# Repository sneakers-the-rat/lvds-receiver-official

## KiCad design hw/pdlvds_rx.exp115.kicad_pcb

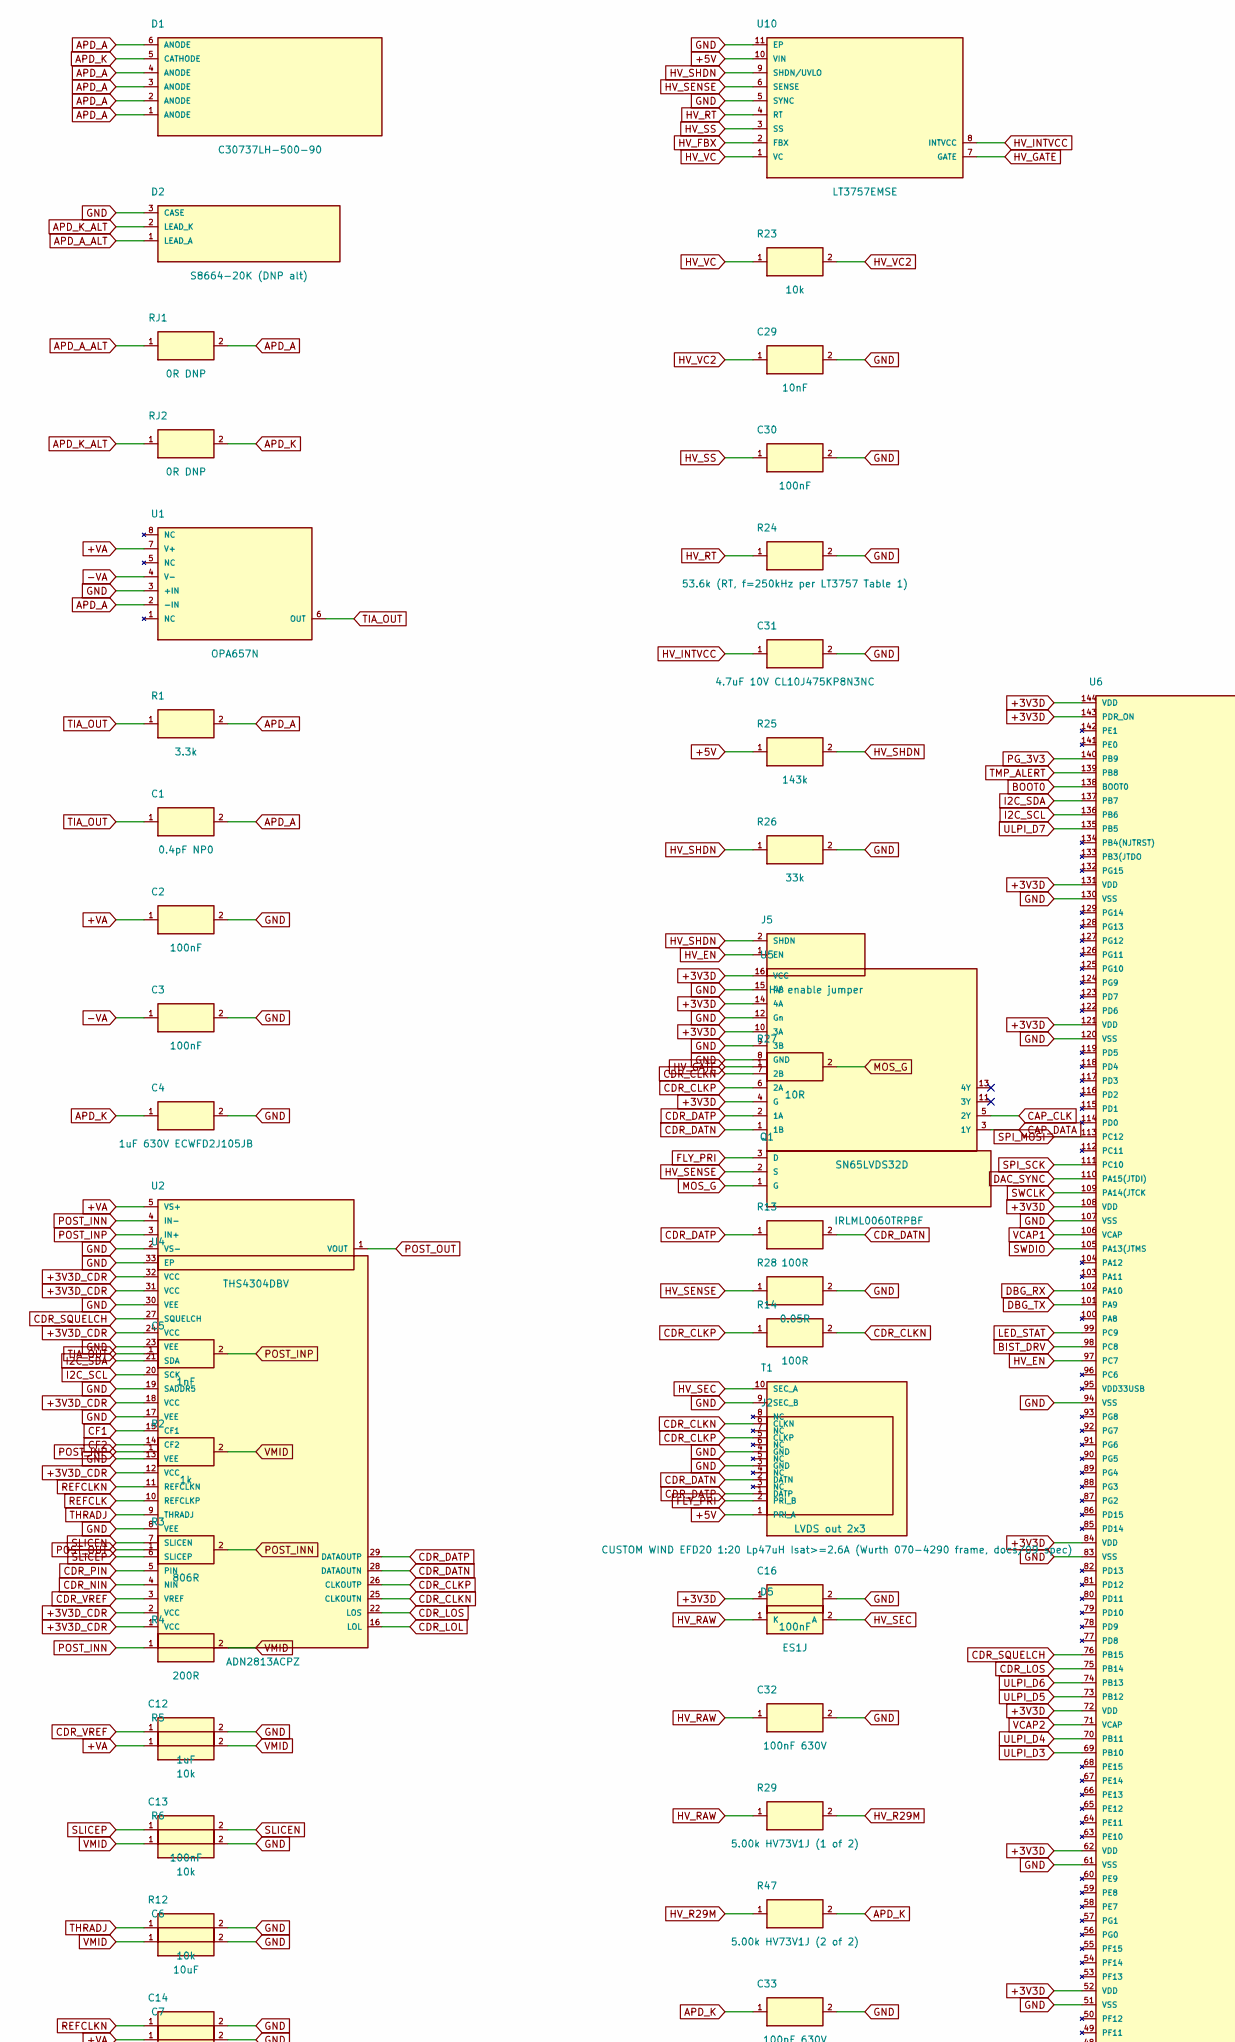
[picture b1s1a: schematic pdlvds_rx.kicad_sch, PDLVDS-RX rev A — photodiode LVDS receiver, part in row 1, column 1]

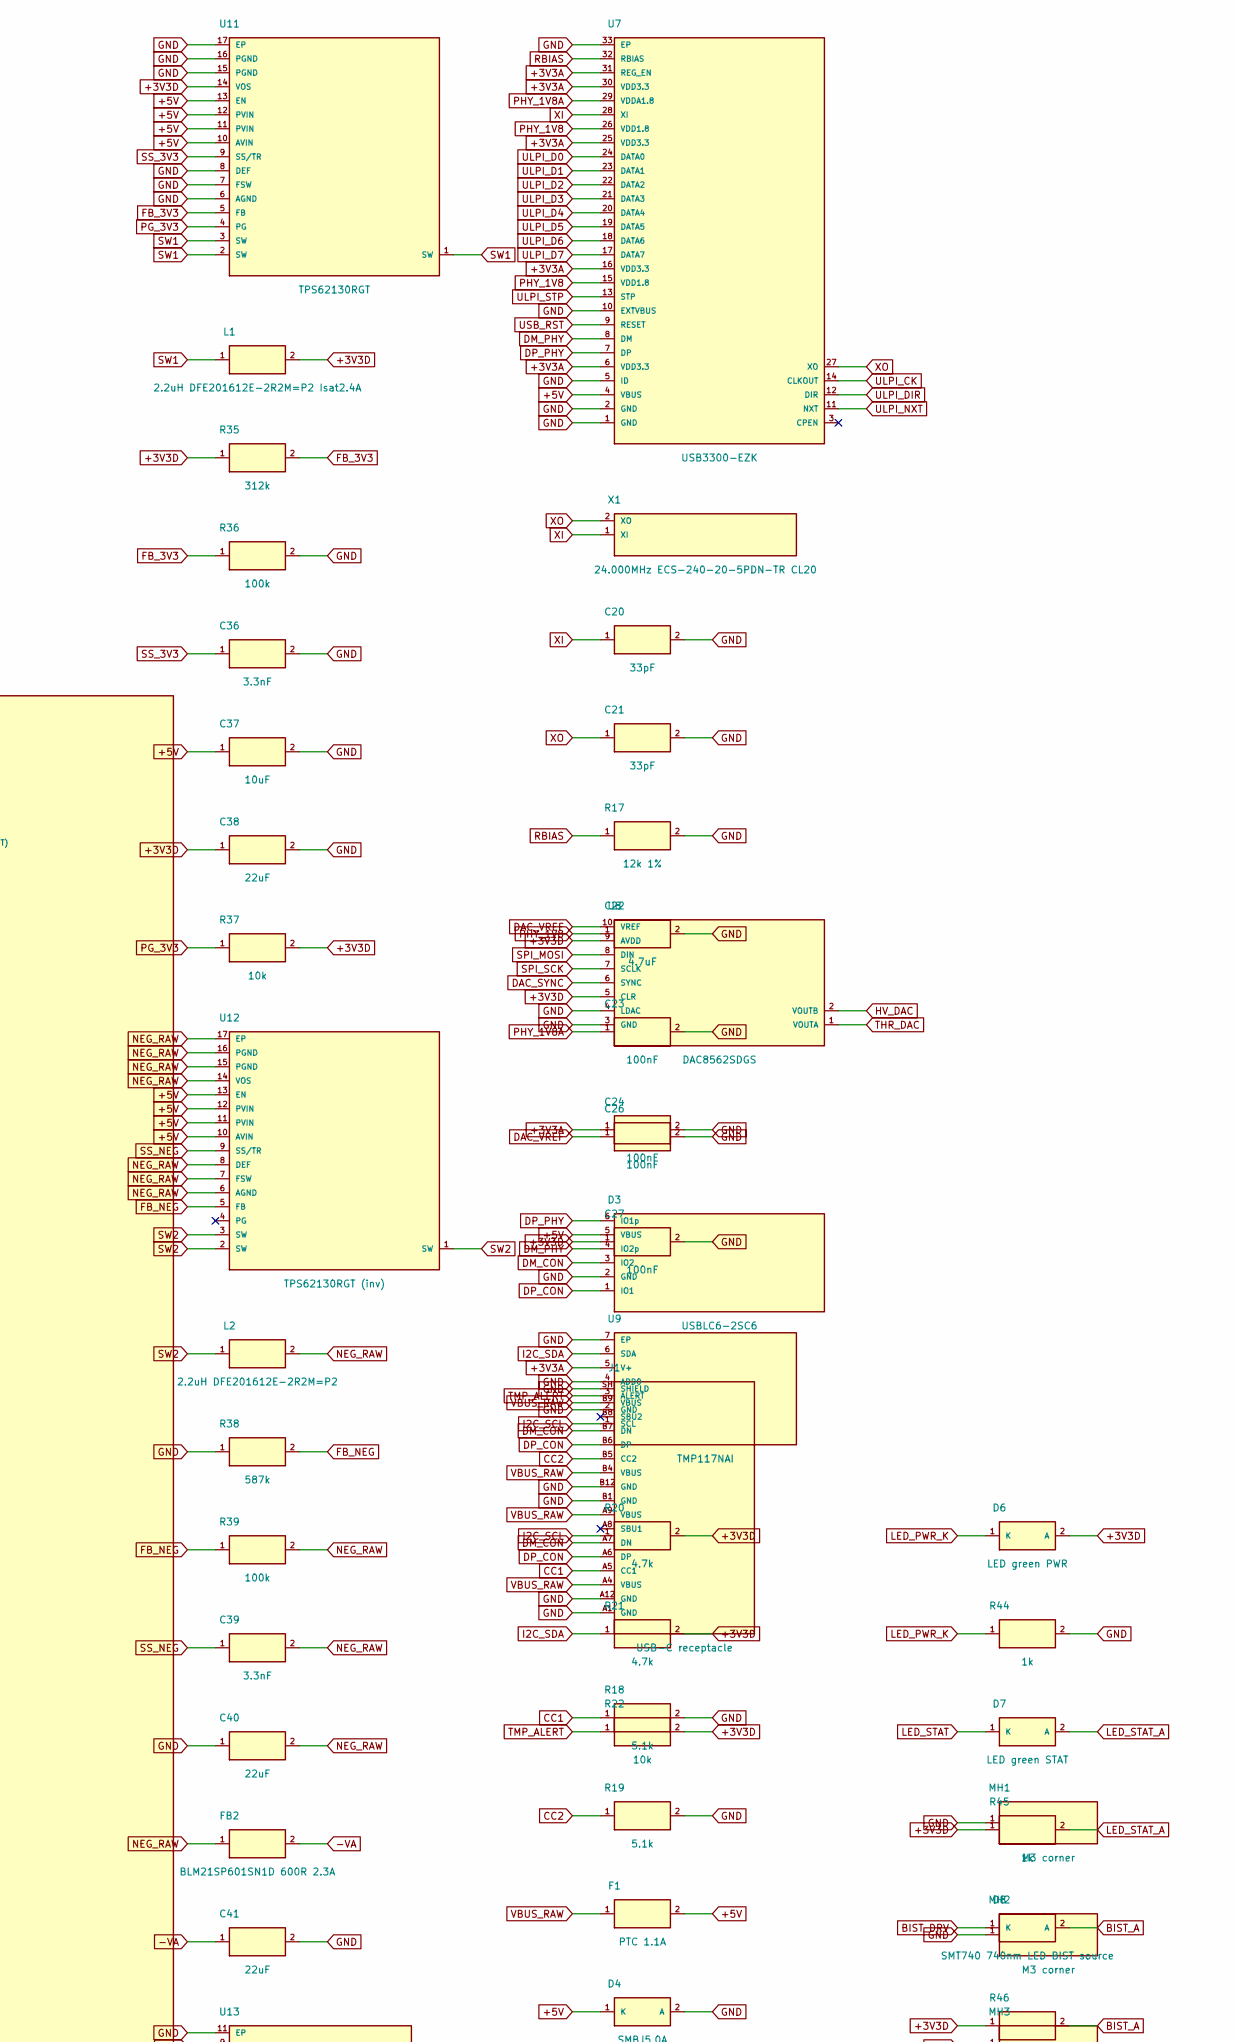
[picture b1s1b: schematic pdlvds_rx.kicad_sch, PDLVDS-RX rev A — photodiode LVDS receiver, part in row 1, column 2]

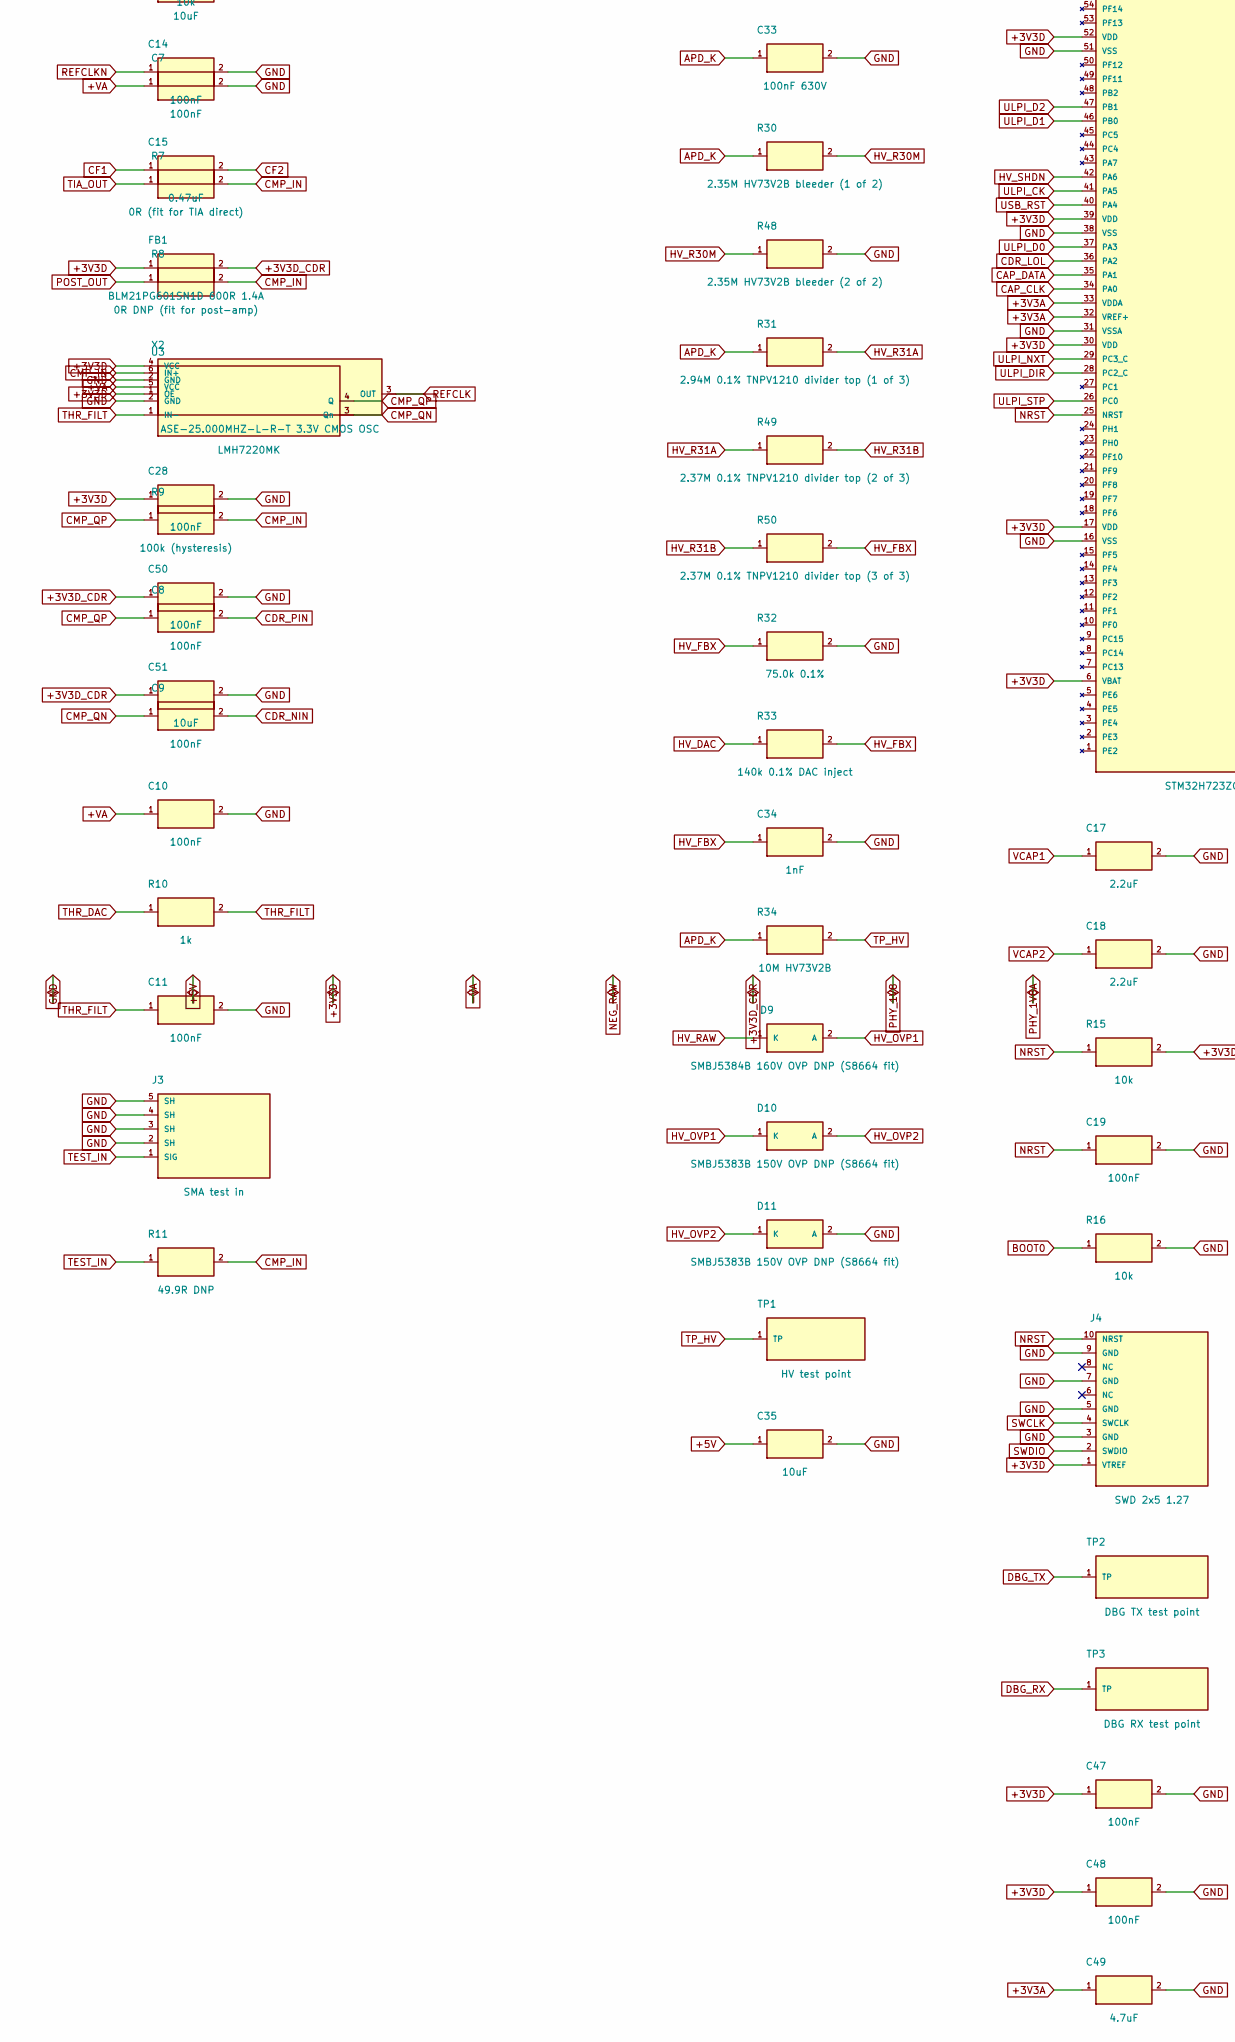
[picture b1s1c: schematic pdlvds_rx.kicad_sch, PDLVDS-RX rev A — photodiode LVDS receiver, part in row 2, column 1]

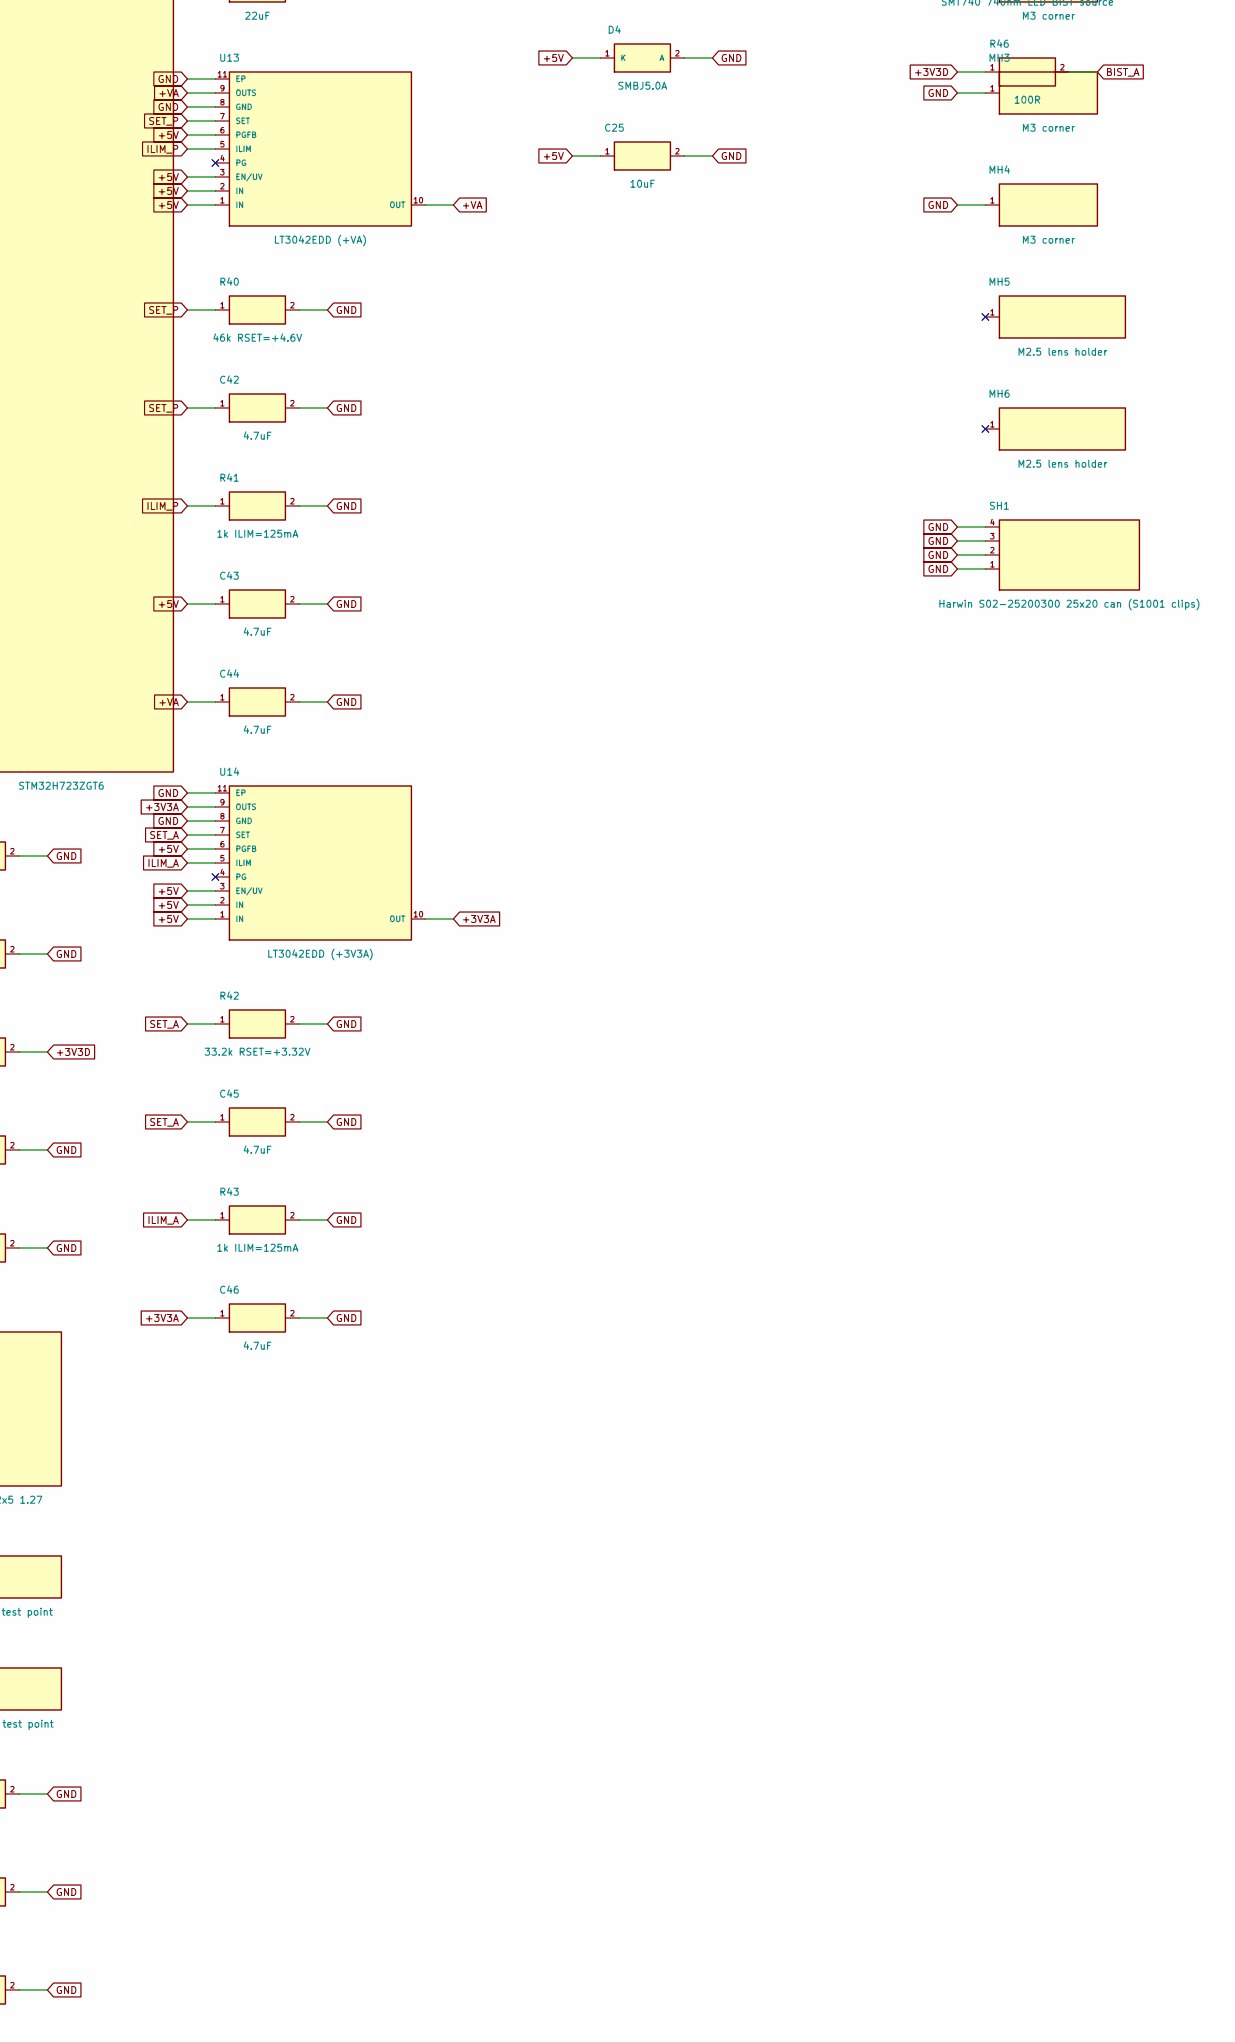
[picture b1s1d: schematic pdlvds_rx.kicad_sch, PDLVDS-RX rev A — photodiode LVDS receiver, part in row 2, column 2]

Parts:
C1: 0.4pF NP0; C_0402_1005Metric
C2, C3, C7, C8, C9, C10, C11, C13, C14, C16, C19, C23, C24, C26, C27, C28, C30, C47, C48, C50: 100nF; C_0603_1608Metric
C4: 1uF 630V ECWFD2J105JB; ECWFD_1uF_630V
C5, C34: 1nF; C_0603_1608Metric
C6, C25, C35, C37, C51: 10uF; C_0805_2012Metric
C12: 1uF; C_0603_1608Metric
C15: 0.47uF; C_0603_1608Metric
C17, C18: 2.2uF; C_0603_1608Metric
C20, C21: 33pF; C_0603_1608Metric
C22, C42, C43, C44, C45, C46, C49: 4.7uF; C_0603_1608Metric
C29: 10nF; C_0603_1608Metric
C31: 4.7uF 10V CL10J475KP8N3NC; C_0603_1608Metric
C32, C33: 100nF 630V; C_1206_3216Metric
C36, C39: 3.3nF; C_0603_1608Metric
C38, C40, C41: 22uF; C_0805_2012Metric
D1: C30737LH-500-90; C30737LH_LCC6
D2: S8664-20K (DNP alt); S8664_TO5
D3: USBLC6-2SC6; SOT-23-6
D4: SMBJ5.0A; D_SMB
D5: ES1J; D_SMA
D6: LED green PWR; LED_0603_1608Metric
D7: LED green STAT; LED_0603_1608Metric
D8: SMT740 740nm LED BIST source; LED_1206_3216Metric
D9: SMBJ5384B 160V OVP DNP (S8664 fit); D_SMB
D10, D11: SMBJ5383B 150V OVP DNP (S8664 fit); D_SMB
F1: PTC 1.1A; Fuse_1812_4532Metric
FB1: BLM21PG601SN1D 600R 1.4A; L_0805_2012Metric
FB2: BLM21SP601SN1D 600R 2.3A; L_0805_2012Metric
J1: USB-C receptacle; USB_C_Receptacle_Amphenol_12401610E4-2A
J2: LVDS out 2x3; PinHeader_2x03_P2.54mm_Vertical
J3: SMA test in; SMA_Amphenol_132134_Vertical
J4: SWD 2x5 1.27; PinHeader_2x05_P1.27mm_Vertical
J5: HV enable jumper; PinHeader_1x02_P2.54mm_Vertical
L1: 2.2uH DFE201612E-2R2M=P2 Isat2.4A; L_Murata_DFE201610P
L2: 2.2uH DFE201612E-2R2M=P2; L_Murata_DFE201610P
MH1, MH2, MH3, MH4: M3 corner; MountingHole_3.2mm_M3
MH5, MH6: M2.5 lens holder; MountingHole_2.7mm_M2.5
Q1: IRLML0060TRPBF; SOT-23
R1: 3.3k; R_0603_1608Metric
R2, R10, R44, R45: 1k; R_0603_1608Metric
R3: 806R; R_0603_1608Metric
R4: 200R; R_0603_1608Metric
R5, R6, R12, R15, R16, R22, R23, R37: 10k; R_0603_1608Metric
R7: 0R (fit for TIA direct); R_0603_1608Metric
R8: 0R DNP (fit for post-amp); R_0603_1608Metric
R9: 100k (hysteresis); R_0603_1608Metric
R11: 49.9R DNP; R_0603_1608Metric
R13, R14, R46: 100R; R_0603_1608Metric
R17: 12k 1%; R_0603_1608Metric
R18, R19: 5.1k; R_0603_1608Metric
R20, R21: 4.7k; R_0603_1608Metric
R24: 53.6k (RT, f=250kHz per LT3757 Table 1); R_0603_1608Metric
R25: 143k; R_0603_1608Metric
R26: 33k; R_0603_1608Metric
R27: 10R; R_0603_1608Metric
R28: 0.05R; R_1206_3216Metric
R29: 5.00k HV73V1J (1 of 2); R_0603_1608Metric
R30: 2.35M HV73V2B bleeder (1 of 2); R_1206_3216Metric
R31: 2.94M 0.1% TNPV1210 divider top (1 of 3); R_1210_3225Metric
R32: 75.0k 0.1%; R_0603_1608Metric
R33: 140k 0.1% DAC inject; R_0603_1608Metric
R34: 10M HV73V2B; R_1206_3216Metric
R35: 312k; R_0603_1608Metric
R36, R39: 100k; R_0603_1608Metric
R38: 587k; R_0603_1608Metric
R40: 46k RSET=+4.6V; R_0603_1608Metric
R41, R43: 1k ILIM=125mA; R_0603_1608Metric
R42: 33.2k RSET=+3.32V; R_0603_1608Metric
R47: 5.00k HV73V1J (2 of 2); R_0603_1608Metric
R48: 2.35M HV73V2B bleeder (2 of 2); R_1206_3216Metric
R49: 2.37M 0.1% TNPV1210 divider top (2 of 3); R_1210_3225Metric
R50: 2.37M 0.1% TNPV1210 divider top (3 of 3); R_1210_3225Metric
RJ1, RJ2: 0R DNP; R_0603_1608Metric
SH1: Harwin S02-25200300 25x20 can (S1001 clips); SHIELD_CAN_26x20
T1: CUSTOM WIND EFD20 1:20 Lp47uH Isat>=2.6A (Wurth 0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; XFMR_EFD20_SMD10
TP1: HV test point; TestPoint_Pad_D1.5mm
TP2: DBG TX test point; TestPoint_Pad_D1.5mm
TP3: DBG RX test point; TestPoint_Pad_D1.5mm
U1: OPA657N; SOIC-8_3.9x4.9mm_P1.27mm
U2: THS4304DBV; SOT-23-5
U3: LMH7220MK; TSOT-23-6
U4: ADN2813ACPZ; QFN-32-1EP_5x5mm_P0.5mm_EP3.1x3.1mm
U5: SN65LVDS32D; SOIC-16_3.9x9.9mm_P1.27mm
U6: STM32H723ZGT6; LQFP-144_20x20mm_P0.5mm
U7: USB3300-EZK; QFN-32-1EP_5x5mm_P0.5mm_EP3.1x3.1mm
U8: DAC8562SDGS; VSSOP-10_3x3mm_P0.5mm
U9: TMP117NAI; TMP117_WSON6
U10: LT3757EMSE; MSOP-10-1EP_3x3mm_P0.5mm_EP1.68x1.88mm
U11: TPS62130RGT; QFN-16-1EP_3x3mm_P0.5mm_EP1.45x1.45mm
U12: TPS62130RGT (inv); QFN-16-1EP_3x3mm_P0.5mm_EP1.45x1.45mm
U13: LT3042EDD (+VA); DFN-10-1EP_3x3mm_P0.5mm_EP1.55x2.48mm
U14: LT3042EDD (+3V3A); DFN-10-1EP_3x3mm_P0.5mm_EP1.55x2.48mm
X1: 24.000MHz ECS-240-20-5PDN-TR CL20; Crystal_SMD_HC49-SD
X2: ASE-25.000MHZ-L-R-T 3.3V CMOS OSC; Oscillator_SMD_Abracon_ASE-4Pin_3.2x2.5mm

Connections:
+3V3A: C24.1, C46.1, C49.1, U6.32 (VREF+), U6.33 (VDDA), U7.6 (VDD3.3), U7.16 (VDD3.3), U7.25 (VDD3.3), U7.30 (VDD3.3), U7.31 (REG_EN), U9.5 (V+), U14.9 (OUTS), U14.10 (OUT); also elsewhere on the board
+3V3D: C16.1, C27.1, C28.1, C38.1, C47.1, C48.1, D6.2 (A), FB1.1, J4.1 (VTREF), L1.2, R15.2, R20.2, R21.2, R22.2, R35.1, R37.2, R45.1, R46.1, U5.4 (G), U5.10 (3A), U5.14 (4A), U5.16 (VCC), U6.6 (VBAT), U6.17 (VDD), U6.30 (VDD), U6.39 (VDD), U6.52 (VDD), U6.62 (VDD), U6.72 (VDD), U6.84 (VDD), U6.108 (VDD), U6.121 (VDD), U6.131 (VDD), U6.143 (PDR_ON), U6.144 (VDD), U8.5 (CLR), U8.9 (AVDD), U11.14 (VOS), X2.1 (OE), X2.4 (VCC)
+3V3D_CDR: C50.1, C51.1, FB1.2, U4.1 (VCC), U4.2 (VCC), U4.12 (VCC), U4.18 (VCC), U4.24 (VCC), U4.31 (VCC), U4.32 (VCC)
+5V: C25.1, C35.1, C37.1, C43.1, D3.5 (VBUS), D4.1 (K), F1.2, R25.1, T1.1 (PRI_A), U7.4 (VBUS), U10.10 (VIN), U11.10 (AVIN), U11.11 (PVIN), U11.12 (PVIN), U11.13 (EN), U12.10 (AVIN), U12.11 (PVIN), U12.12 (PVIN), U12.13 (EN), U13.1 (IN), U13.2 (IN), U13.3 (EN/UV), U13.6 (PGFB), U14.1 (IN), U14.2 (IN), U14.3 (EN/UV), U14.6 (PGFB); also elsewhere on the board
+VA: C2.1, C7.1, C10.1, C44.1, R5.1, U1.7 (V+), U2.5 (VS+), U3.5 (VCC), U13.9 (OUTS), U13.10 (OUT)
-VA: C3.1, C41.1, FB2.2, U1.4 (V-)
APD_A: C1.2, D1.1 (ANODE), D1.2 (ANODE), D1.3 (ANODE), D1.4 (ANODE), D1.6 (ANODE), R1.2, RJ1.2, U1.2 (-IN); also elsewhere on the board
APD_A_ALT: D2.1 (LEAD_A), RJ1.1; also elsewhere on the board
APD_K: C4.1, C33.1, D1.5 (CATHODE), R30.1, R31.1, R34.1, R47.2, RJ2.2; also elsewhere on the board
APD_K_ALT: D2.2 (LEAD_K), RJ2.1; also elsewhere on the board
BIST_A: D8.2 (A), R46.2
BIST_DRV: D8.1 (K), U6.98 (PC8)
BOOT0: R16.1, U6.138 (BOOT0)
CAP_CLK: U5.5 (2Y), U6.34 (PA0)
CAP_DATA: U5.3 (1Y), U6.35 (PA1)
CC1: J1.A5 (CC1), R18.1
CC2: J1.B5 (CC2), R19.1
CDR_CLKN: J2.6 (CLKN), R14.2, U4.25 (CLKOUTN), U5.7 (2B)
CDR_CLKP: J2.5 (CLKP), R14.1, U4.26 (CLKOUTP), U5.6 (2A)
CDR_DATN: J2.2 (DATN), R13.2, U4.28 (DATAOUTN), U5.1 (1B)
CDR_DATP: J2.1 (DATP), R13.1, U4.29 (DATAOUTP), U5.2 (1A)
CDR_LOL: U4.16 (LOL), U6.36 (PA2)
CDR_LOS: U4.22 (LOS), U6.75 (PB14)
CDR_NIN: C9.2, U4.4 (NIN)
CDR_PIN: C8.2, U4.5 (PIN)
CDR_SQUELCH: U4.27 (SQUELCH), U6.76 (PB15)
CDR_VREF: C12.1, U4.3 (VREF)
CF1: C15.1, U4.15 (CF1)
CF2: C15.2, U4.14 (CF2)
CMP_IN: R7.2, R8.2, R9.2, R11.2, U3.6 (IN+)
CMP_QN: C9.1, U3.3 (Qn)
CMP_QP: C8.1, R9.1, U3.4 (Q)
DAC_SYNC: U6.110 (PA15(JTDI)), U8.6 (SYNC)
DAC_VREF: C26.1, U8.10 (VREF)
DBG_RX: TP3.1, U6.102 (PA10)
DBG_TX: TP2.1, U6.101 (PA9)
DM_CON: D3.3 (IO2), J1.A7 (DN), J1.B7 (DN)
DM_PHY: D3.4 (IO2p), U7.8 (DM)
DP_CON: D3.1 (IO1), J1.A6 (DP), J1.B6 (DP)
DP_PHY: D3.6 (IO1p), U7.7 (DP)
FB_3V3: R35.2, R36.1, U11.5 (FB)
FB_NEG: R38.2, R39.1, U12.5 (FB)
FLY_PRI: Q1.3 (D), T1.2 (PRI_B); also elsewhere on the board
GND: C2.2, C3.2, C4.2, C6.2, C7.2, C10.2, C11.2, C12.2, C14.2, C16.2, C17.2, C18.2, C19.2, C20.2, C21.2, C22.2, C23.2, C24.2, C25.2, C26.2, C27.2, C28.2, C29.2, C30.2, C31.2, C32.2, C33.2, C34.2, C35.2, C36.2, C37.2, C38.2, C40.1, C41.2, C42.2, C43.2, C44.2, C45.2, C46.2, C47.2, C48.2, C49.2, C50.2, C51.2, D2.3 (CASE), D3.2 (GND), D4.2 (A), D11.2 (A), J1.A1 (GND), J1.A12 (GND), J1.B1 (GND), J1.B12 (GND), J1.SH (SHIELD), J2.3 (GND), J2.4 (GND), J3.2 (SH), J3.3 (SH), J3.4 (SH), J3.5 (SH), J4.3 (GND), J4.5 (GND), J4.7 (GND), J4.9 (GND), MH1.1, MH2.1, MH3.1, MH4.1, R6.2, R12.2, R16.2, R17.2, R18.2, R19.2, R24.2, R26.2, R28.2, R32.2, R36.2, R38.1, R40.2, R41.2, R42.2, R43.2, R44.2, R48.2, SH1.1, SH1.2, SH1.3, SH1.4, T1.9 (SEC_B), U1.3 (+IN), U2.2 (VS-), U3.2 (GND), U4.8 (VEE), U4.13 (VEE), U4.17 (VEE), U4.19 (SADDR5), U4.23 (VEE), U4.30 (VEE), U4.33 (EP), U5.8 (GND), U5.9 (3B), U5.12 (Gn), U5.15 (4B), U6.16 (VSS), U6.31 (VSSA), U6.38 (VSS), U6.51 (VSS), U6.61 (VSS), U6.83 (VSS), U6.94 (VSS), U6.107 (VSS), U6.120 (VSS), U6.130 (VSS), U7.1 (GND), U7.2 (GND), U7.5 (ID), U7.10 (EXTVBUS), U7.33 (EP), U8.3 (GND), U8.4 (LDAC), U9.2 (GND), U9.4 (ADD0), U9.7 (EP), U10.5 (SYNC), U10.11 (EP), U11.6 (AGND), U11.7 (FSW), U11.8 (DEF), U11.15 (PGND), U11.16 (PGND), U11.17 (EP), U13.8 (GND), U13.11 (EP), U14.8 (GND), U14.11 (EP), X2.2 (GND); also elsewhere on the board
HV_DAC: R33.1, U8.2 (VOUTB)
HV_EN: J5.1 (EN), U6.97 (PC7)
HV_FBX: C34.1, R32.1, R33.2, R50.2, U10.2 (FBX)
HV_GATE: R27.1, U10.7 (GATE)
HV_INTVCC: C31.1, U10.8 (INTVCC)
HV_OVP1: D9.2 (A), D10.1 (K)
HV_OVP2: D10.2 (A), D11.1 (K)
HV_R29M: R29.2, R47.1
HV_R30M: R30.2, R48.1
HV_R31A: R31.2, R49.1
HV_R31B: R49.2, R50.1
HV_RAW: C32.1, D5.1 (K), D9.1 (K), R29.1
HV_RT: R24.1, U10.4 (RT)
HV_SEC: D5.2 (A), T1.10 (SEC_A); also elsewhere on the board
HV_SENSE: Q1.2 (S), R28.1, U10.6 (SENSE)
HV_SHDN: J5.2 (SHDN), R25.2, R26.1, U6.42 (PA6), U10.9 (SHDN/UVLO)
HV_SS: C30.1, U10.3 (SS)
HV_VC: R23.1, U10.1 (VC)
HV_VC2: C29.1, R23.2
I2C_SCL: R20.1, U4.20 (SCK), U6.136 (PB6), U9.1 (SCL); also elsewhere on the board
I2C_SDA: R21.1, U4.21 (SDA), U6.137 (PB7), U9.6 (SDA); also elsewhere on the board
ILIM_A: R43.1, U14.5 (ILIM)
ILIM_P: R41.1, U13.5 (ILIM)
LED_PWR_K: D6.1 (K), R44.1
LED_STAT: D7.1 (K), U6.99 (PC9)
LED_STAT_A: D7.2 (A), R45.2
MOS_G: Q1.1 (G), R27.2
NEG_RAW: C39.2, C40.2, FB2.1, L2.2, R39.2, U12.6 (AGND), U12.7 (FSW), U12.8 (DEF), U12.14 (VOS), U12.15 (PGND), U12.16 (PGND), U12.17 (EP)
NRST: C19.1, J4.10 (NRST), R15.1, U6.25 (NRST)
PG_3V3: R37.1, U6.140 (PB9), U11.4 (PG)
PHY_1V8: C22.1, U7.15 (VDD1.8), U7.26 (VDD1.8)
PHY_1V8A: C23.1, U7.29 (VDDA1.8)
POST_INN: R3.2, R4.1, U2.4 (IN-)
POST_INP: C5.2, R2.1, U2.3 (IN+)
POST_OUT: R3.1, R8.1, U2.1 (VOUT)
RBIAS: R17.1, U7.32 (RBIAS)
REFCLK: U4.10 (REFCLKP), X2.3 (OUT)
REFCLKN: C14.1, U4.11 (REFCLKN)
SET_A: C45.1, R42.1, U14.7 (SET)
SET_P: C42.1, R40.1, U13.7 (SET)
SLICEN: C13.2, U4.7 (SLICEN)
SLICEP: C13.1, U4.6 (SLICEP)
SPI_MOSI: U6.113 (PC12), U8.8 (DIN)
SPI_SCK: U6.111 (PC10), U8.7 (SCLK)
SS_3V3: C36.1, U11.9 (SS/TR)
SS_NEG: C39.1, U12.9 (SS/TR)
SW1: L1.1, U11.1 (SW), U11.2 (SW), U11.3 (SW)
SW2: L2.1, U12.1 (SW), U12.2 (SW), U12.3 (SW)
SWCLK: J4.4 (SWCLK), U6.109 (PA14(JTCK)
SWDIO: J4.2 (SWDIO), U6.105 (PA13(JTMS)
TEST_IN: J3.1 (SIG), R11.1
THRADJ: R12.1, U4.9 (THRADJ)
THR_DAC: R10.1, U8.1 (VOUTA)
THR_FILT: C11.1, R10.2, U3.1 (IN-)
TIA_OUT: C1.1, C5.1, R1.1, R7.1, U1.6 (OUT)
TMP_ALERT: R22.1, U6.139 (PB8), U9.3 (ALERT); also elsewhere on the board
TP_HV: R34.2, TP1.1
ULPI_CK: U6.41 (PA5), U7.14 (CLKOUT)
ULPI_D0: U6.37 (PA3), U7.24 (DATA0)
ULPI_D1: U6.46 (PB0), U7.23 (DATA1)
ULPI_D2: U6.47 (PB1), U7.22 (DATA2)
ULPI_D3: U6.69 (PB10), U7.21 (DATA3)
ULPI_D4: U6.70 (PB11), U7.20 (DATA4)
ULPI_D5: U6.73 (PB12), U7.19 (DATA5)
ULPI_D6: U6.74 (PB13), U7.18 (DATA6)
ULPI_D7: U6.135 (PB5), U7.17 (DATA7)
ULPI_DIR: U6.28 (PC2_C), U7.12 (DIR)
ULPI_NXT: U6.29 (PC3_C), U7.11 (NXT)
ULPI_STP: U6.26 (PC0), U7.13 (STP)
USB_RST: U6.40 (PA4), U7.9 (RESET)
VBUS_RAW: F1.1, J1.A4 (VBUS), J1.A9 (VBUS), J1.B4 (VBUS), J1.B9 (VBUS)
VCAP1: C17.1, U6.106 (VCAP)
VCAP2: C18.1, U6.71 (VCAP)
VMID: C6.1, R2.2, R4.2, R5.2, R6.1
XI: C20.1, U7.28 (XI), X1.1 (XI)
XO: C21.1, U7.27 (XO), X1.2 (XO)

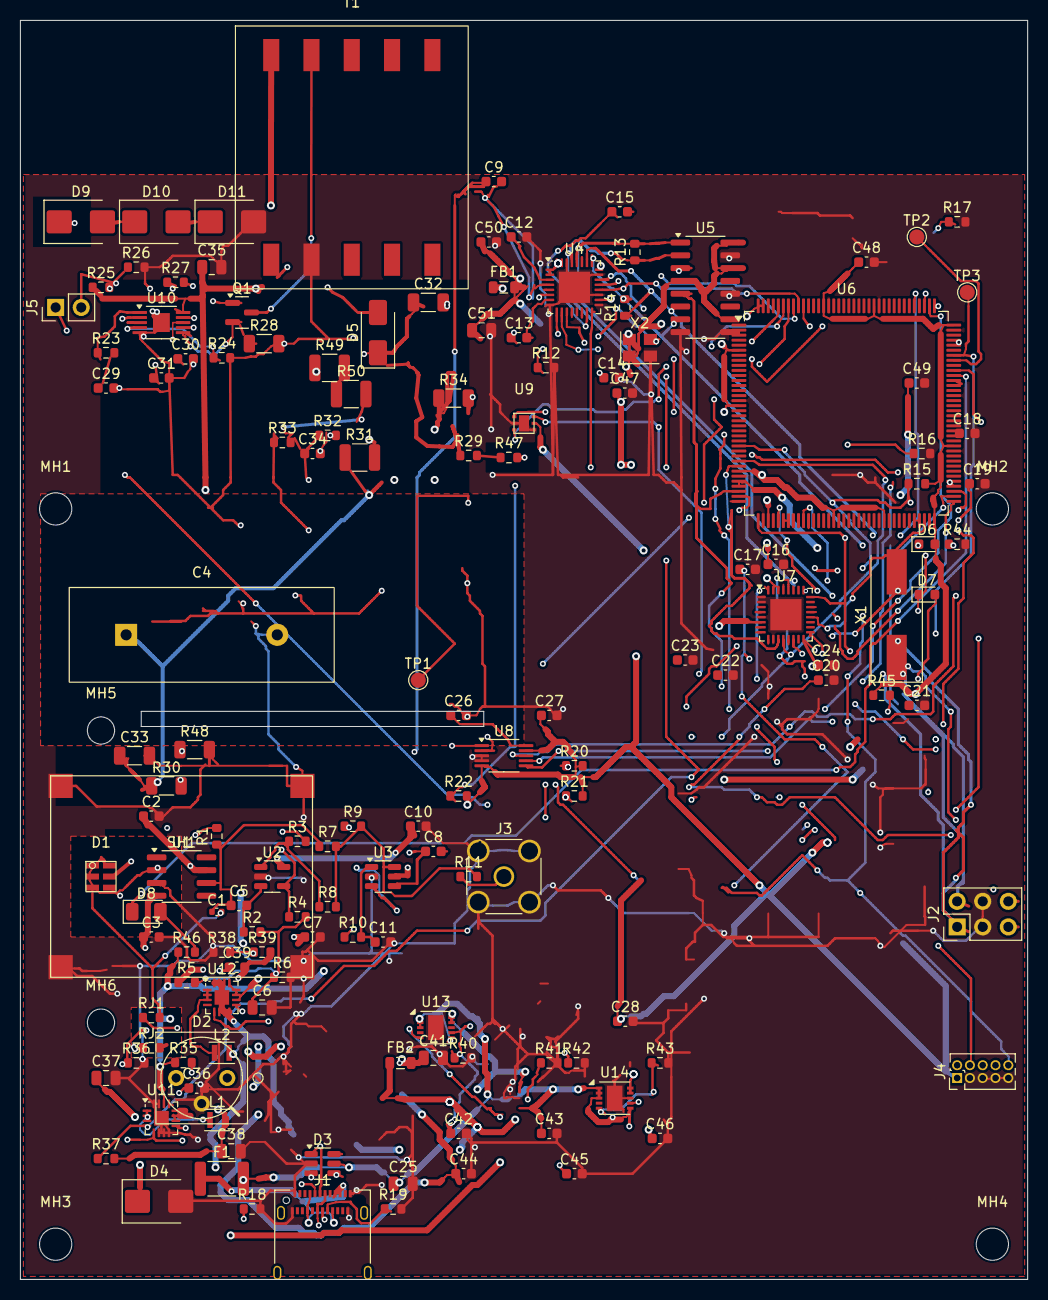
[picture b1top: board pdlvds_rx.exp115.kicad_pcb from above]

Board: 4 copper layers, 100.0 x 125.0 mm, 152 parts (1 on the bottom side), 120 nets.

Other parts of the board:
C: ECWFD2J105JB; ECWFD_1uF_630V
D: S8664; S8664_TO5
D#2: C30737LH; C30737LH_LCC6
SH: SHIELD; SHIELD_CAN_26x20
T: EFD20 custom wind; XFMR_EFD20_SMD10
U: TMP117; TMP117_WSON6

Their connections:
+3V3A: U.5; also elsewhere on the board
+5V: T.1; also elsewhere on the board
APD_A: D#2.1, D#2.2, D#2.3, D#2.4, D#2.6; also elsewhere on the board
APD_A_ALT: D.1; also elsewhere on the board
APD_K: C.1, D#2.5; also elsewhere on the board
APD_K_ALT: D.2; also elsewhere on the board
FLY_PRI: T.2; also elsewhere on the board
GND: C.2, D.3, SH.1, SH.2, SH.3, SH.4, T.9, U.2, U.4, U.7; also elsewhere on the board
HV_SEC: T.10; also elsewhere on the board
I2C_SCL: U.1; also elsewhere on the board
I2C_SDA: U.6; also elsewhere on the board
TMP_ALERT: U.3; also elsewhere on the board

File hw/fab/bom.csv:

Refs,Qty,Value,Footprint
C1,1,0.4pF NP0,Capacitor_SMD:C_0402_1005Metric
C15,1,0.47uF,Capacitor_SMD:C_0603_1608Metric
C17 C18,2,2.2uF,Capacitor_SMD:C_0603_1608Metric
C2 C3 C7 C8 C9 C10 C11 C13 C14 C16 C19 C23 C24 C26 C27 C28 C30 C47 C48 C50,20,100nF,Capacitor_SMD:C_0603_1608Metric
C20 C21,2,18pF,Capacitor_SMD:C_0603_1608Metric
C22 C31 C42 C43 C44 C45 C46 C49,8,4.7uF,Capacitor_SMD:C_0603_1608Metric
C29,1,10nF,Capacitor_SMD:C_0603_1608Metric
C32 C33,2,100nF 630V,Capacitor_SMD:C_1206_3216Metric
C36 C39,2,3.3nF,Capacitor_SMD:C_0603_1608Metric
C38 C40 C41,3,22uF,Capacitor_SMD:C_0805_2012Metric
C4 C12,2,1uF,Capacitor_SMD:C_0603_1608Metric
C5 C34,2,1nF,Capacitor_SMD:C_0603_1608Metric
C6 C25 C35 C37 C51,5,10uF,Capacitor_SMD:C_0805_2012Metric
D1,1,C30737LH-500-90,pdlvds:C30737LH_LCC6
D2,1,S8664-20K (DNP alt),pdlvds:S8664_TO5
D3,1,USBLC6-2SC6,Package_TO_SOT_SMD:SOT-23-6
D4,1,SMBJ5.0A,Diode_SMD:D_SMA
D5,1,ES1J,Diode_SMD:D_SMA
D6,1,LED green PWR,LED_SMD:LED_0603_1608Metric
D7,1,LED green STAT,LED_SMD:LED_0603_1608Metric
D8,1,LED 740nm BIST source,LED_SMD:LED_1206_3216Metric
F1,1,PTC 1.1A,Fuse:Fuse_1812_4532Metric
FB1 FB2,2,600R@100MHz,Inductor_SMD:L_0805_2012Metric
J1,1,USB-C receptacle,Connector_USB:USB_C_Receptacle_Amphenol_12401610E4-2A
J2,1,LVDS out 2x3,Connector_PinHeader_2.54mm:PinHeader_2x03_P2.54mm_Vertical
J3,1,SMA test in,Connector_Coaxial:SMA_Amphenol_132134_Vertical
J4,1,SWD 2x5 1.27,Connector_PinHeader_1.27mm:PinHeader_2x05_P1.27mm_Vertical
J5,1,HV enable jumper,Connector_PinHeader_2.54mm:PinHeader_1x02_P2.54mm_Vertical
L1 L2,2,2.2uH,Inductor_SMD:L_0805_2012Metric
MH1 MH2 MH3 MH4,4,M3 corner,MountingHole:MountingHole_3.2mm_M3
MH5 MH6,2,M2.5 lens holder,MountingHole:MountingHole_2.7mm_M2.5
Q1,1,IRLML0030 SOT-23,Package_TO_SOT_SMD:SOT-23
R1,1,3.3k,Resistor_SMD:R_0603_1608Metric
R11,1,49.9R DNP,Resistor_SMD:R_0603_1608Metric
R13 R14 R46,3,100R,Resistor_SMD:R_0603_1608Metric
R17,1,12k 1%,Resistor_SMD:R_0603_1608Metric
R18 R19,2,5.1k,Resistor_SMD:R_0603_1608Metric
R2 R10 R44 R45,4,1k,Resistor_SMD:R_0603_1608Metric
R20 R21,2,4.7k,Resistor_SMD:R_0603_1608Metric
R24,1,"24.9k (RT, VERIFY f=250k)",Resistor_SMD:R_0603_1608Metric
R25,1,143k,Resistor_SMD:R_0603_1608Metric
R26,1,33k,Resistor_SMD:R_0603_1608Metric
R28,1,0.05R,Resistor_SMD:R_1206_3216Metric
R29,1,10k HV,Resistor_SMD:R_1206_3216Metric
R3,1,806R,Resistor_SMD:R_0603_1608Metric
R30,1,4.7M bleeder,Resistor_SMD:R_1206_3216Metric
R31,1,7.68M 0.1% HV divider top,Resistor_SMD:R_1206_3216Metric
R32,1,75.0k 0.1%,Resistor_SMD:R_0603_1608Metric
R33,1,140k 0.1% DAC inject,Resistor_SMD:R_0603_1608Metric
R34,1,10M HV probe,Resistor_SMD:R_1206_3216Metric
R35,1,312k,Resistor_SMD:R_0603_1608Metric
R36 R39,2,100k,Resistor_SMD:R_0603_1608Metric
R38,1,587k,Resistor_SMD:R_0603_1608Metric
R4,1,200R,Resistor_SMD:R_0603_1608Metric
R40,1,46k RSET=+4.6V,Resistor_SMD:R_0603_1608Metric
R41 R43,2,1k ILIM=125mA,Resistor_SMD:R_0603_1608Metric
R42,1,33.2k RSET=+3.32V,Resistor_SMD:R_0603_1608Metric
R5 R6 R12 R15 R16 R22 R23 R27 R37,9,10k,Resistor_SMD:R_0603_1608Metric
R7,1,0R (fit for TIA direct),Resistor_SMD:R_0603_1608Metric
R8,1,0R DNP (fit for post-amp),Resistor_SMD:R_0603_1608Metric
R9,1,100k (hysteresis),Resistor_SMD:R_0603_1608Metric
RJ1 RJ2,2,0R DNP,Resistor_SMD:R_0603_1608Metric
SH1,1,Shield can frontend,pdlvds:SHIELD_CAN_26x20
T1,1,Flyback xfmr 1:20,pdlvds:XFMR_FLYBACK_6P
TP1,1,HV test point,TestPoint:TestPoint_Pad_D1.5mm
TP2,1,DBG TX test point,TestPoint:TestPoint_Pad_D1.5mm
TP3,1,DBG RX test point,TestPoint:TestPoint_Pad_D1.5mm
U1,1,OPA657N,Package_SO:SOIC-8_3.9x4.9mm_P1.27mm
U10,1,LT3757EMSE,Package_SO:MSOP-10-1EP_3x3mm_P0.5mm_EP1.68x1.88mm
U11,1,TPS62130RGT,Package_DFN_QFN:QFN-16-1EP_3x3mm_P0.5mm_EP1.45x1.45mm
U12,1,TPS62130RGT (inv),Package_DFN_QFN:QFN-16-1EP_3x3mm_P0.5mm_EP1.45x1.45mm
U13,1,LT3042EDD (+VA),Package_DFN_QFN:DFN-10-1EP_3x3mm_P0.5mm_EP1.55x2.48mm
U14,1,LT3042EDD (+3V3A),Package_DFN_QFN:DFN-10-1EP_3x3mm_P0.5mm_EP1.55x2.48mm
U2,1,THS4304DBV,Package_TO_SOT_SMD:SOT-23-5
U3,1,LMH7220MK,Package_TO_SOT_SMD:TSOT-23-6
U4,1,ADN2813ACPZ,Package_DFN_QFN:QFN-32-1EP_5x5mm_P0.5mm_EP3.1x3.1mm
U5,1,SN65LVDS32D,Package_SO:SOIC-16_3.9x9.9mm_P1.27mm
U6,1,STM32H723ZGT6,Package_QFP:LQFP-144_20x20mm_P0.5mm
U7,1,USB3300-EZK,Package_DFN_QFN:QFN-32-1EP_5x5mm_P0.5mm_EP3.1x3.1mm
U8,1,DAC8562SDGS,Package_SO:VSSOP-10_3x3mm_P0.5mm
U9,1,TMP117NAI,pdlvds:TMP117_WSON6
X1,1,24MHz,Crystal:Crystal_SMD_3225-4Pin_3.2x2.5mm
X2,1,25MHz OSC,Oscillator:Oscillator_SMD_Abracon_ASE-4Pin_3.2x2.5mm
